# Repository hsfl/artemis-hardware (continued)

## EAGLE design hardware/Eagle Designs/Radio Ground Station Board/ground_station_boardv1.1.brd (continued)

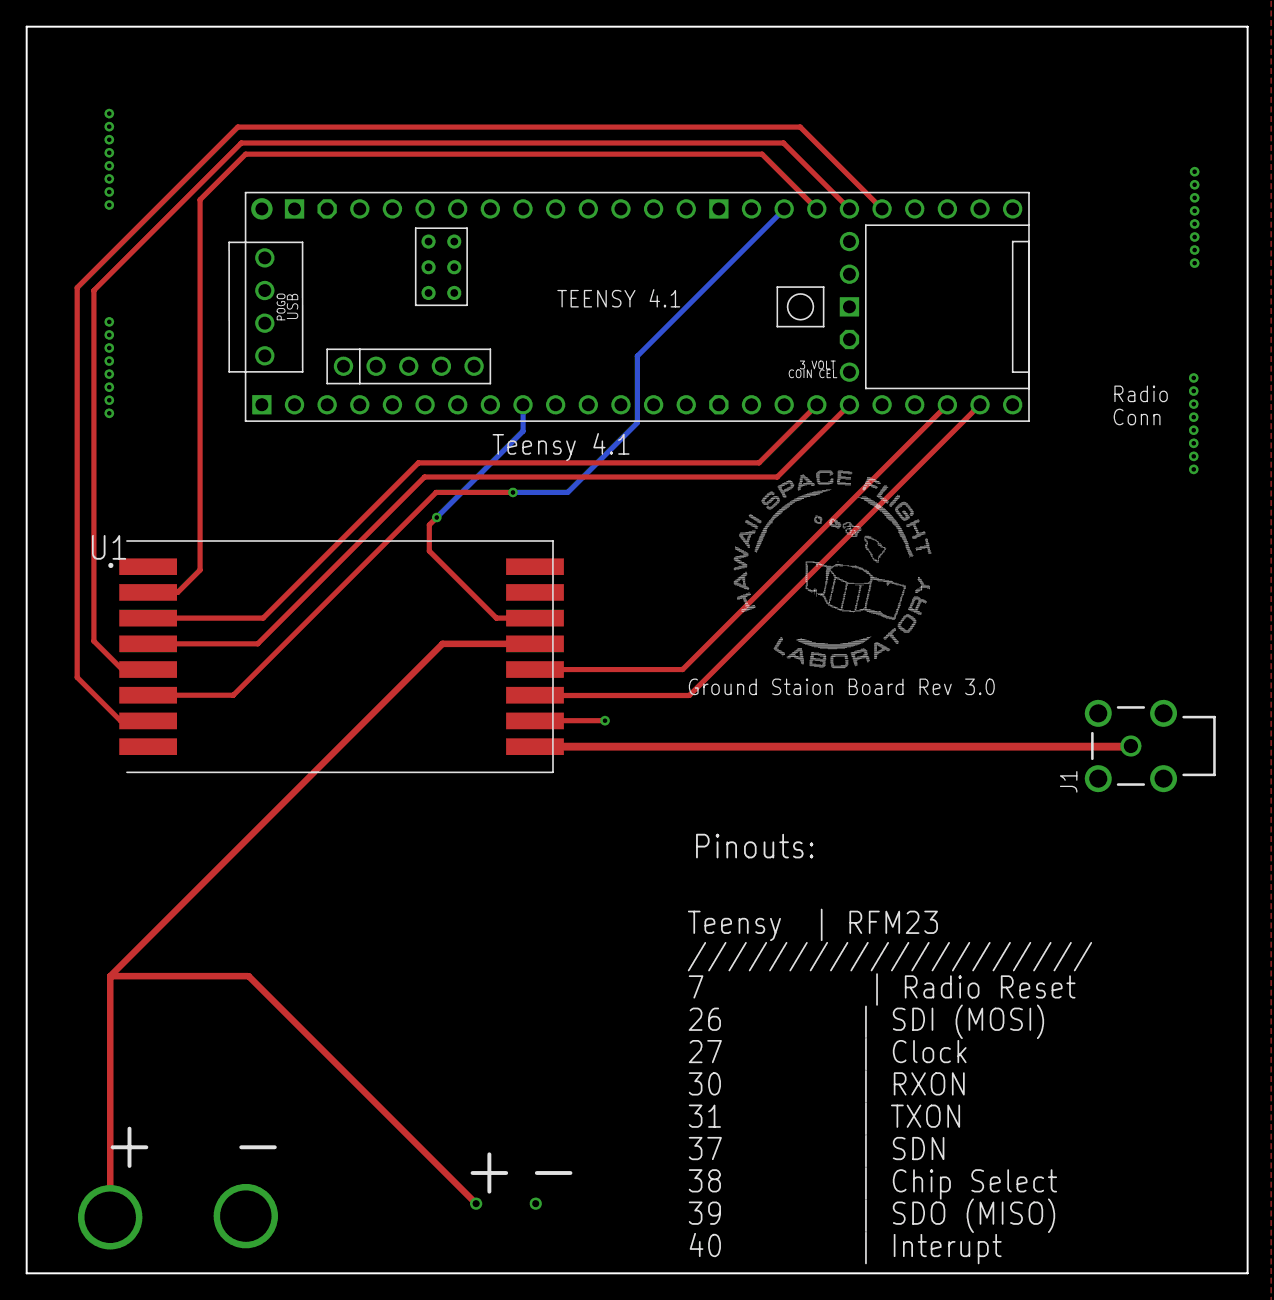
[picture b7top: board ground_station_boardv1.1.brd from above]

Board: 4 copper layers, 95.0 x 97.0 mm, 3 parts (0 on the bottom side), 12 nets.

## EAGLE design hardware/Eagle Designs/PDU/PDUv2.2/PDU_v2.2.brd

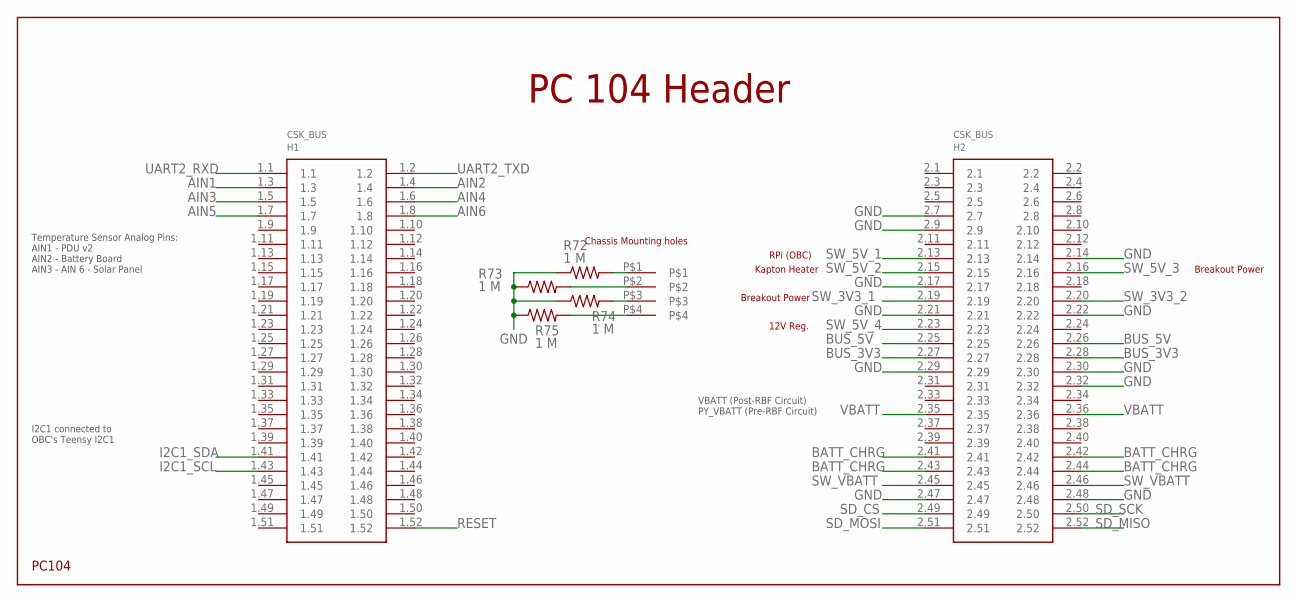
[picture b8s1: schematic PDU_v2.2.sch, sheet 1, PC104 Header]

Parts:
H1: PC104_WCONN
R72, R73, R74, R75: 1 M; 0603-RES

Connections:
AIN1: H1.1.3; also elsewhere on the board
AIN2: H1.1.4; also elsewhere on the board
AIN3: H1.1.5; also elsewhere on the board
AIN4: H1.1.6; also elsewhere on the board
AIN5: H1.1.7; also elsewhere on the board
AIN6: H1.1.8; also elsewhere on the board
BATT_CHRG: H1.2.41, H1.2.42, H1.2.43, H1.2.44; also elsewhere on the board
BUS_3V3: H1.2.27, H1.2.28; also elsewhere on the board
BUS_5V: H1.2.25, H1.2.26; also elsewhere on the board
GND: H1.2.7, H1.2.9, H1.2.14, H1.2.17, H1.2.21, H1.2.22, H1.2.29, H1.2.30, H1.2.32, H1.2.47, H1.2.48, R72.1, R73.1, R74.1, R75.1; also elsewhere on the board
I2C1_SCL: H1.1.43; also elsewhere on the board
I2C1_SDA: H1.1.41; also elsewhere on the board
unnamed: H1.P$1, R72.2
unnamed: H1.P$4, R75.2
unnamed: H1.P$2, R73.2
unnamed: H1.P$3, R74.2
RESET: H1.1.52; also elsewhere on the board
SD_CS: H1.2.49; also elsewhere on the board
SD_MISO: H1.2.52; also elsewhere on the board
SD_MOSI: H1.2.51; also elsewhere on the board
SD_SCK: H1.2.50; also elsewhere on the board
SW_3V3_1: H1.2.19; also elsewhere on the board
SW_3V3_2: H1.2.20; also elsewhere on the board
SW_5V_1: H1.2.13; also elsewhere on the board
SW_5V_2: H1.2.15; also elsewhere on the board
SW_5V_3: H1.2.16; also elsewhere on the board
SW_5V_4: H1.2.23; also elsewhere on the board
SW_VBATT: H1.2.45, H1.2.46; also elsewhere on the board
UART2_RXD: H1.1.1; also elsewhere on the board
UART2_TXD: H1.1.2; also elsewhere on the board
VBATT: H1.2.35, H1.2.36; also elsewhere on the board

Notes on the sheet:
PC 104 Header
Temperature Sensor Analog Pins: AIN1 - PDU v2 AIN2 - Battery Board AIN3 - AIN 6 - Solar Panel
VBATT (Post-RBF Circuit) PY_VBATT (Pre-RBF Circuit)
Kapton Heater
RPi (OBC)
12V Reg.
Breakout Power
I2C1 connected to OBC's Teensy I2C1

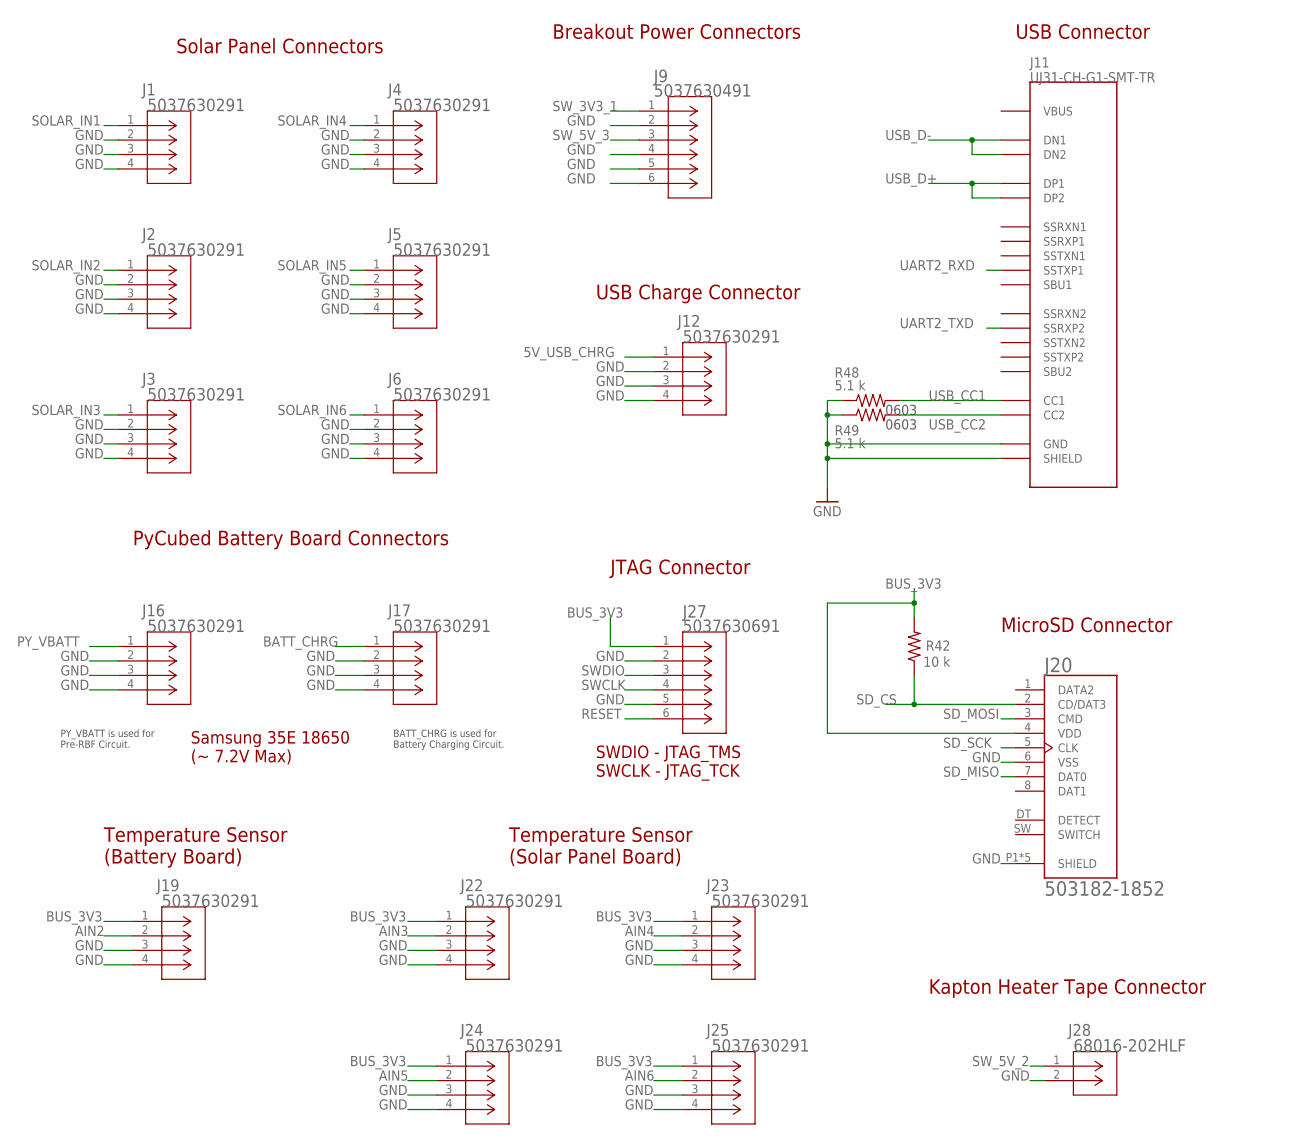
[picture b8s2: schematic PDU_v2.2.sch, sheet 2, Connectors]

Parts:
J1, J2, J3, J4, J5, J6, J12, J16, J17, J19, J22, J23, J24, J25: 5037630291; CON_5037630291
J9: 5037630491; CON_5037630491
J11: UJ31-CH-G1-SMT-TR; CUI_UJ31-CH-G1-SMT-TR
J20: 503182-1852; MOLEX_503182-1852
J27: 5037630691; CONN_503763-0691_MOL
J28: 68016-202HLF
R42: 10 k; 0603-RES
R48, R49: 5.1 k; 0603-RES

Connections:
5V_USB_CHRG: J12.1; also elsewhere on the board
AIN2: J19.2; also elsewhere on the board
AIN3: J22.2; also elsewhere on the board
AIN4: J23.2; also elsewhere on the board
AIN5: J24.2; also elsewhere on the board
AIN6: J25.2; also elsewhere on the board
BATT_CHRG: J17.1; also elsewhere on the board
BUS_3V3: J19.1, J20.4 (VDD), J22.1, J23.1, J24.1, J25.1, J27.1, R42.2; also elsewhere on the board
GND: J1.2, J1.3, J1.4, J2.2, J2.3, J2.4, J3.2, J3.3, J3.4, J4.2, J4.3, J4.4, J5.2, J5.3, J5.4, J6.2, J6.3, J6.4, J9.2, J9.4, J9.5, J9.6, J11.A1 (GND), J11.A12 (GND), J11.B1 (GND), J11.B12 (GND), J11.SH1 (SHIELD), J11.SH2 (SHIELD), J11.SH3 (SHIELD), J11.SH4 (SHIELD), J11.SH5 (SHIELD), J11.SH6 (SHIELD), J12.2, J12.3, J12.4, J16.2, J16.3, J16.4, J17.2, J17.3, J17.4, J19.3, J19.4, J20.6 (VSS), J20.P1 (SHIELD), J20.P2 (SHIELD), J20.P3 (SHIELD), J20.P4 (SHIELD), J20.P5 (SHIELD), J22.3, J22.4, J23.3, J23.4, J24.3, J24.4, J25.3, J25.4, J27.2, J27.5, J28.2, R48.1, R49.1; also elsewhere on the board
PY_VBATT: J16.1; also elsewhere on the board
RESET: J27.6; also elsewhere on the board
SD_CS: J20.2 (CD/DAT3), R42.1; also elsewhere on the board
SD_MISO: J20.7 (DAT0); also elsewhere on the board
SD_MOSI: J20.3 (CMD); also elsewhere on the board
SD_SCK: J20.5 (CLK); also elsewhere on the board
SOLAR_IN1: J1.1; also elsewhere on the board
SOLAR_IN2: J2.1; also elsewhere on the board
SOLAR_IN3: J3.1; also elsewhere on the board
SOLAR_IN4: J4.1; also elsewhere on the board
SOLAR_IN5: J5.1; also elsewhere on the board
SOLAR_IN6: J6.1; also elsewhere on the board
SWCLK: J27.4; also elsewhere on the board
SWDIO: J27.3; also elsewhere on the board
SW_3V3_1: J9.1; also elsewhere on the board
SW_5V_2: J28.1; also elsewhere on the board
SW_5V_3: J9.3; also elsewhere on the board
UART2_RXD: J11.A2 (SSTXP1); also elsewhere on the board
UART2_TXD: J11.A11 (SSRXP2); also elsewhere on the board
USB_CC1: J11.A5 (CC1), R48.2
USB_CC2: J11.B5 (CC2), R49.2
USB_D+: J11.A6 (DP1), J11.B6 (DP2); also elsewhere on the board
USB_D-: J11.A7 (DN1), J11.B7 (DN2); also elsewhere on the board
VBUS: J11.A4 (VBUS), J11.A9 (VBUS), J11.B4 (VBUS), J11.B9 (VBUS)

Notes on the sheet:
USB Charge Connector
Solar Panel Connectors
Breakout Power Connectors
USB Connector
MicroSD Connector
JTAG Connector
SWDIO - JTAG_TMS SWCLK - JTAG_TCK
PyCubed Battery Board Connectors
Samsung 35E 18650 (~ 7.2V Max)
Kapton Heater Tape Connector
Temperature Sensor (Solar Panel Board)
Temperature Sensor (Battery Board)
0603
PY_VBATT is used for Pre-RBF Circuit.
BATT_CHRG is used for Battery Charging Circuit.

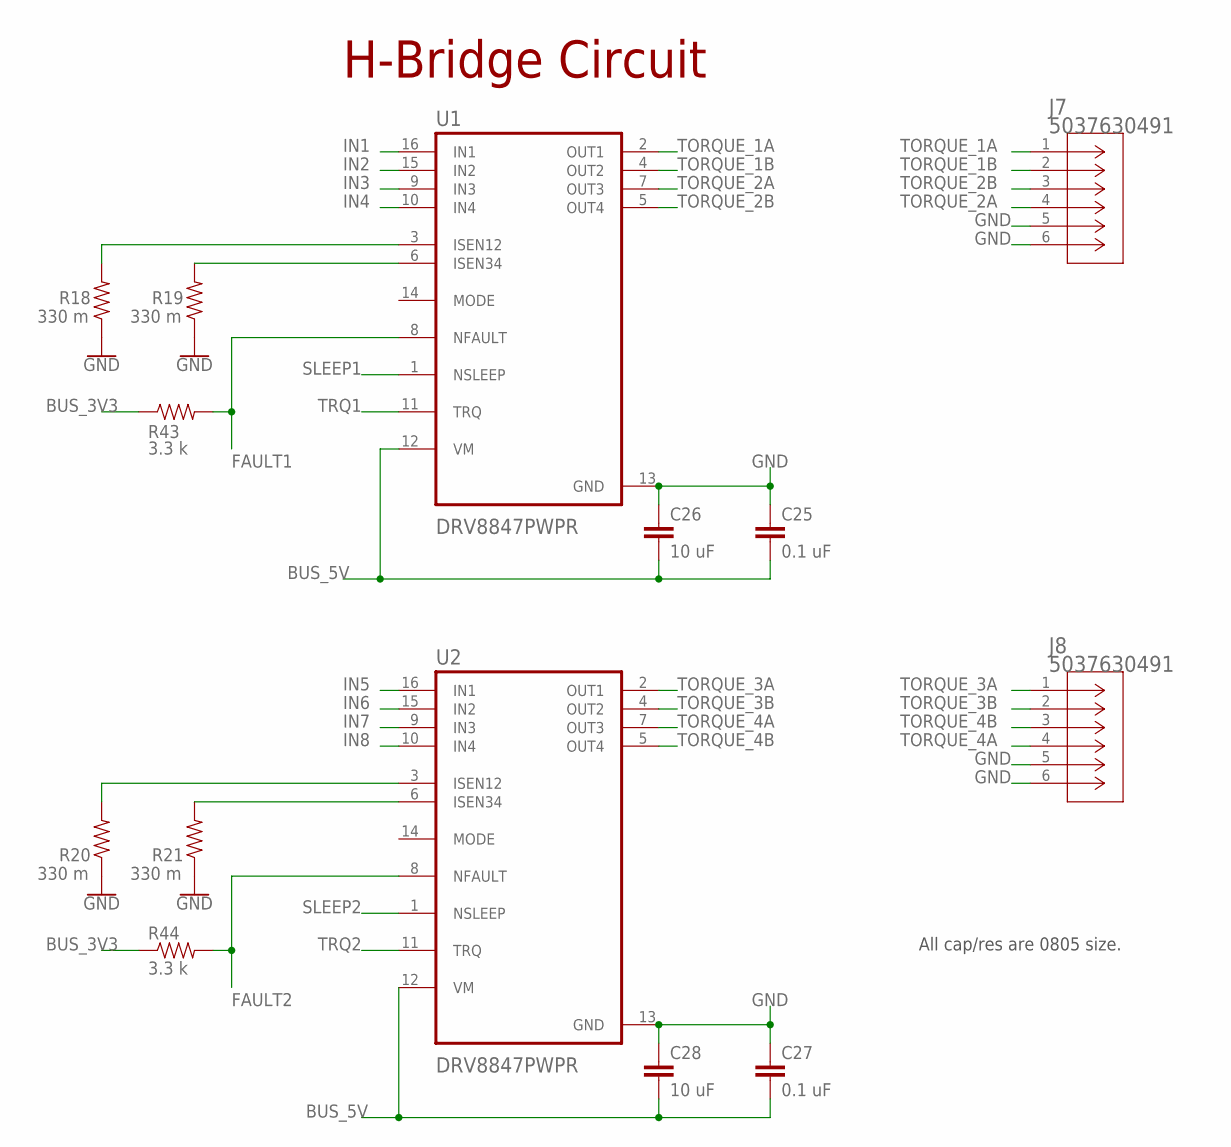
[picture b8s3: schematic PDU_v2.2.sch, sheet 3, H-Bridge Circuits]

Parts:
C25, C27: 0.1 uF; 0805
C26, C28: 10 uF; 0805
J7, J8: 5037630491; CON_5037630491
R18, R19, R20, R21: 330 m; 0805
R43, R44: 3.3 k; 0805
U1, U2: DRV8847PWPR; SOP65P640X120-17N

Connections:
BUS_3V3: R43.1, R44.1; also elsewhere on the board
BUS_5V: C25.2, C26.2, C27.2, C28.2, U1.12 (VM), U2.12 (VM); also elsewhere on the board
FAULT1: R43.2, U1.8 (NFAULT); also elsewhere on the board
FAULT2: R44.2, U2.8 (NFAULT); also elsewhere on the board
GND: C25.1, C26.1, C27.1, C28.1, J7.5, J7.6, J8.5, J8.6, R18.1, R19.1, R20.1, R21.1, U1.13 (GND), U2.13 (GND); also elsewhere on the board
IN1: U1.16 (IN1); also elsewhere on the board
IN2: U1.15 (IN2); also elsewhere on the board
IN3: U1.9 (IN3); also elsewhere on the board
IN4: U1.10 (IN4); also elsewhere on the board
IN5: U2.16 (IN1); also elsewhere on the board
IN6: U2.15 (IN2); also elsewhere on the board
IN7: U2.9 (IN3); also elsewhere on the board
IN8: U2.10 (IN4); also elsewhere on the board
unnamed: R19.2, U1.6 (ISEN34)
unnamed: R18.2, U1.3 (ISEN12)
unnamed: R21.2, U2.6 (ISEN34)
unnamed: R20.2, U2.3 (ISEN12)
SLEEP1: U1.1 (NSLEEP); also elsewhere on the board
SLEEP2: U2.1 (NSLEEP); also elsewhere on the board
TORQUE_1A: J7.1, U1.2 (OUT1)
TORQUE_1B: J7.2, U1.4 (OUT2)
TORQUE_2A: J7.4, U1.7 (OUT3)
TORQUE_2B: J7.3, U1.5 (OUT4)
TORQUE_3A: J8.1, U2.2 (OUT1)
TORQUE_3B: J8.2, U2.4 (OUT2)
TORQUE_4A: J8.4, U2.7 (OUT3)
TORQUE_4B: J8.3, U2.5 (OUT4)
TRQ1: U1.11 (TRQ); also elsewhere on the board
TRQ2: U2.11 (TRQ); also elsewhere on the board

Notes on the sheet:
H-Bridge Circuit
All cap/res are 0805 size.

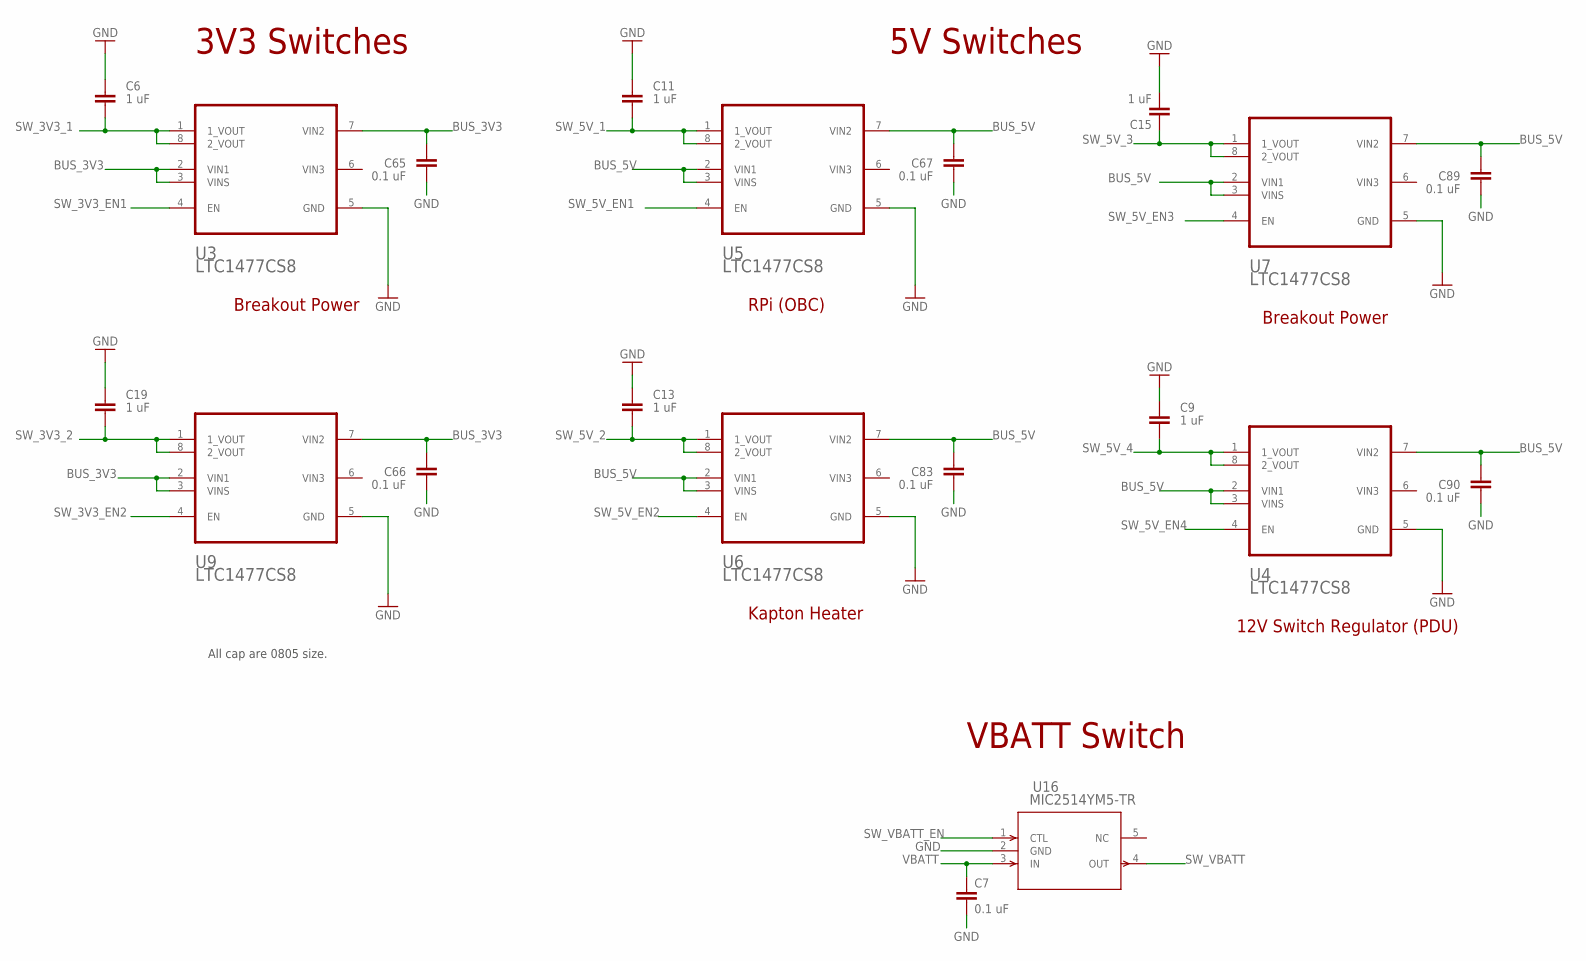
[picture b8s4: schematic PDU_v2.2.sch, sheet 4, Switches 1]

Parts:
C6, C9, C11, C13, C15, C19: 1 uF; 0805
C7, C65, C66, C67, C83, C89, C90: 0.1 uF; 0805
U3, U4, U5, U6, U7, U9: LTC1477CS8LINEAR_TECHNOLOGY_LTC1477CS8_0_2; LINEAR_TECHNOLOGY_LTC1477CS8_2
U16: MIC2514YM5-TR; SOT-23-5_M5_MCH

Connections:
BUS_3V3: C65.1, C66.1, U3.2 (VIN1), U3.3 (VINS), U3.7 (VIN2), U9.2 (VIN1), U9.3 (VINS), U9.7 (VIN2); also elsewhere on the board
BUS_5V: C67.1, C83.1, C89.1, C90.1, U4.2 (VIN1), U4.3 (VINS), U4.7 (VIN2), U5.2 (VIN1), U5.3 (VINS), U5.7 (VIN2), U6.2 (VIN1), U6.3 (VINS), U6.7 (VIN2), U7.2 (VIN1), U7.3 (VINS), U7.7 (VIN2); also elsewhere on the board
GND: C6.2, C7.2, C9.2, C11.2, C13.2, C15.2, C19.2, C65.2, C66.2, C67.2, C83.2, C89.2, C90.2, U3.5 (GND), U4.5 (GND), U5.5 (GND), U6.5 (GND), U7.5 (GND), U9.5 (GND), U16.2 (GND); also elsewhere on the board
SW_3V3_1: C6.1, U3.1 (1_VOUT), U3.8 (2_VOUT); also elsewhere on the board
SW_3V3_2: C19.1, U9.1 (1_VOUT), U9.8 (2_VOUT); also elsewhere on the board
SW_3V3_EN1: U3.4 (EN); also elsewhere on the board
SW_3V3_EN2: U9.4 (EN); also elsewhere on the board
SW_5V_1: C11.1, U5.1 (1_VOUT), U5.8 (2_VOUT); also elsewhere on the board
SW_5V_2: C13.1, U6.1 (1_VOUT), U6.8 (2_VOUT); also elsewhere on the board
SW_5V_3: C15.1, U7.1 (1_VOUT), U7.8 (2_VOUT); also elsewhere on the board
SW_5V_4: C9.1, U4.1 (1_VOUT), U4.8 (2_VOUT); also elsewhere on the board
SW_5V_EN1: U5.4 (EN); also elsewhere on the board
SW_5V_EN2: U6.4 (EN); also elsewhere on the board
SW_5V_EN3: U7.4 (EN); also elsewhere on the board
SW_5V_EN4: U4.4 (EN); also elsewhere on the board
SW_VBATT: U16.4 (OUT); also elsewhere on the board
SW_VBATT_EN: U16.1 (CTL); also elsewhere on the board
VBATT: C7.1, U16.3 (IN); also elsewhere on the board
VIN3: U3.6 (VIN3), U4.6 (VIN3), U5.6 (VIN3), U6.6 (VIN3), U7.6 (VIN3), U9.6 (VIN3)

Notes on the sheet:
3V3 Switches
5V Switches
Breakout Power
RPi (OBC)
Kapton Heater
All cap are 0805 size.
12V Switch Regulator (PDU)
VBATT Switch

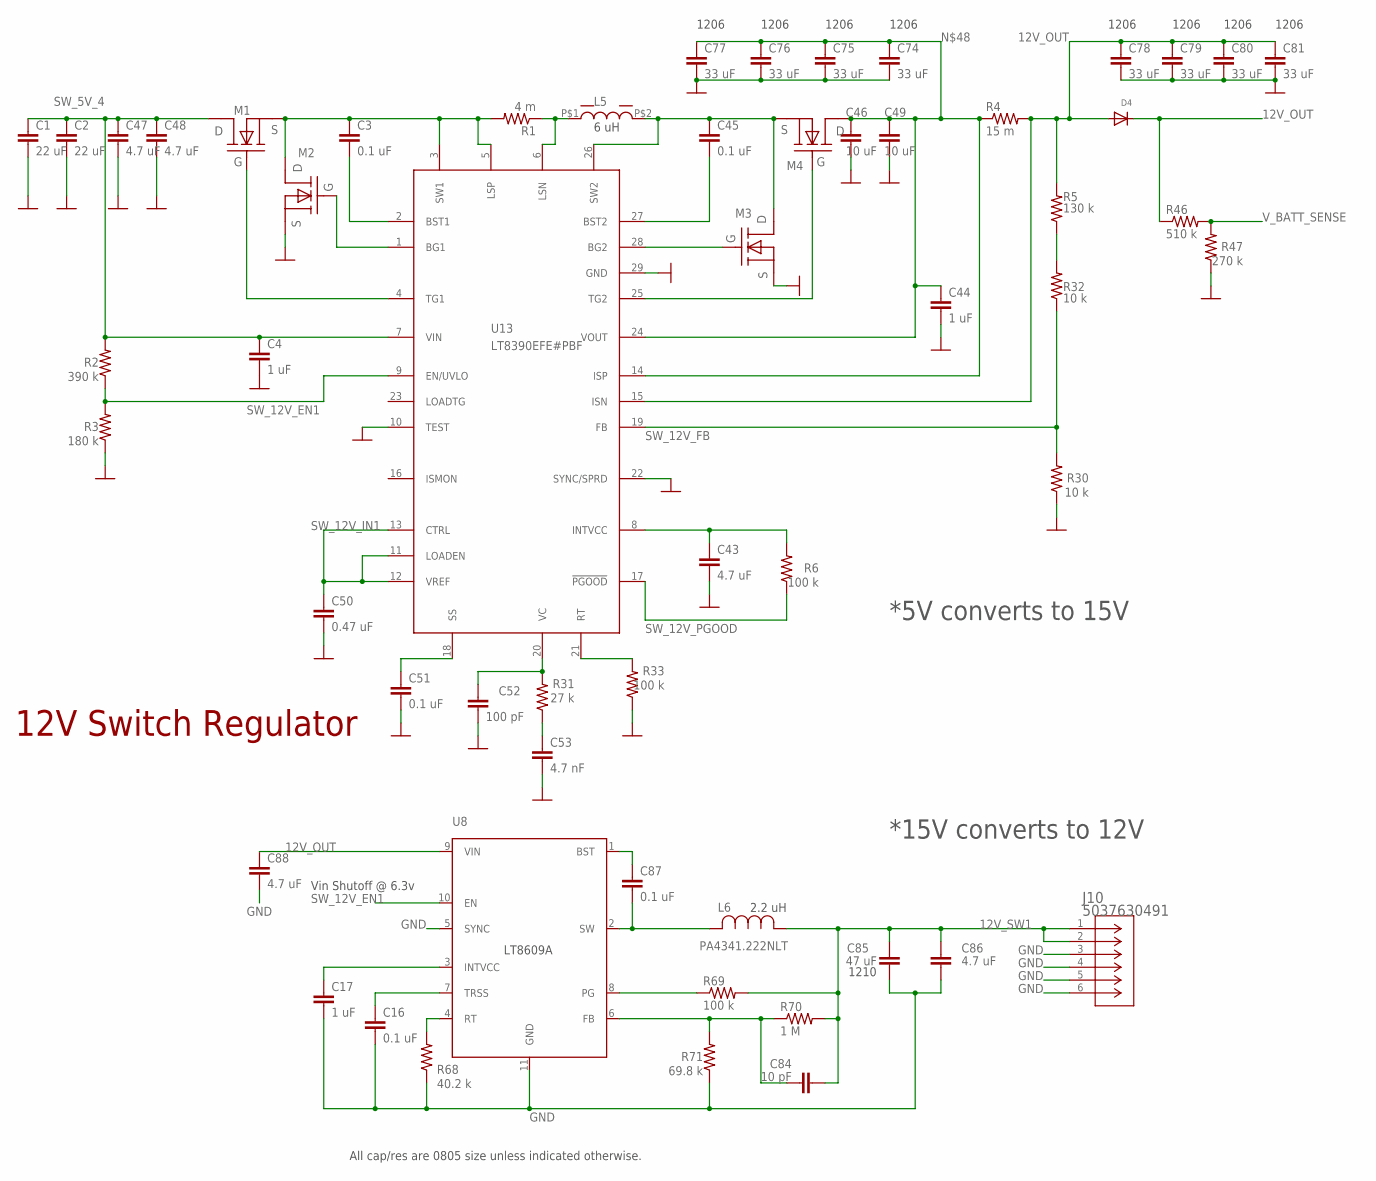
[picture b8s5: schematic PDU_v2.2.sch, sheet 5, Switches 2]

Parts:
C1, C2: 22 uF; 0805
C3, C16, C45, C51, C87: 0.1 uF; 0805
C4, C17, C44: 1 uF; 0805
C43, C47, C48, C86, C88: 4.7 uF; 0805
C46, C49: 10 uF; 0805
C50: 0.47 uF; 0805
C52: 100 pF; 0805
C53: 4.7 nF; 0805
C74, C75, C76, C77, C78, C79, C80, C81: 33 uF; 1206
C84: 10 pF; 0805
C85: 47 uF; 1210
D4: DIODE_SOD-123FL; SOD-123FL
J10: 5037630491; CON_5037630491
L5: 6 uH; 7443551600
L6: PA4341.222NLT; IND_222NLT_PUL
M1, M2: BSZ100N06LS3
M3, M4: BSZ033NE2LS5; BSZ100N06LS3
R1: 4 m; 0805
R2: 390 k; 0805
R3: 180 k; 0805
R4: 15 m; 0805
R5: 130 k; 0805
R6, R33, R69: 100 k; 0805
R30, R32: 10 k; 0805
R31: 27 k; 0805
R46: 510 k; 0805
R47: 270 k; 0805
R68: 40.2 k; 0805
R70: 1 M; 0805
R71: 69.8 k; 0805
U8: LT8609A; MSOP-10_MSE
U13: LT8390EFE#PBF; SOP65P640X120-29N

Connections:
12V_OUT: C78.1, C79.1, C80.1, C81.1, C88.1, D4.A, D4.C, R4.2, R5.2, R46.1, U8.9 (VIN), U13.15 (ISN)
12V_SW1: C84.2, C85.1, C86.1, J10.1, J10.2, L6.1, R69.2, R70.2
BST_3V3_BUS: C87.1, U8.1 (BST)
FB_3V3_BUS: C84.1, R70.1, R71.2, U8.6 (FB)
GND: C1.2, C2.2, C4.2, C16.2, C17.2, C43.2, C44.2, C46.2, C47.2, C48.2, C49.2, C50.2, C51.2, C52.2, C53.2, C74.2, C75.2, C76.2, C77.2, C78.2, C79.2, C80.2, C81.2, C85.2, C86.2, C88.2, J10.3, J10.4, J10.5, J10.6, M2.P$2 (S), M2.P$3 (S), M2.P$4 (S), M3.P$2 (S), M3.P$3 (S), M3.P$4 (S), R3.1, R30.1, R33.1, R47.1, R68.1, R71.1, U8.5 (SYNC), U8.11 (GND), U13.10 (TEST), U13.22 (SYNC/SPRD), U13.29 (GND); also elsewhere on the board
unnamed: C3.1, M1.P$2 (S), M1.P$3 (S), M1.P$4 (S), M2.P$5 (D), M2.P$6 (D), M2.P$7 (D), M2.P$8 (D), M2.P$9 (D), R1.2, U13.3 (SW1), U13.5 (LSP)
unnamed: C3.2, U13.2 (BST1)
unnamed: M2.P$1 (G), U13.1 (BG1)
unnamed: M1.P$1 (G), U13.4 (TG1)
unnamed: M3.P$1 (G), U13.28 (BG2)
unnamed: C52.1, R31.2, U13.20 (VC)
unnamed: R5.1, R32.2
unnamed: C45.1, L5.P$2, M3.P$5 (D), M3.P$6 (D), M3.P$7 (D), M3.P$8 (D), M3.P$9 (D), M4.P$2 (S), M4.P$3 (S), M4.P$4 (S), U13.26 (SW2)
unnamed: C43.1, R6.2, U13.8 (INTVCC)
unnamed: L5.P$1, R1.1, U13.6 (LSN)
unnamed: C45.2, U13.27 (BST2)
unnamed: C44.1, C46.1, C49.1, C74.1, C75.1, C76.1, C77.1, M4.P$5 (D), M4.P$6 (D), M4.P$7 (D), M4.P$8 (D), M4.P$9 (D), R4.1, U13.14 (ISP), U13.24 (VOUT)
unnamed: M4.P$1 (G), U13.25 (TG2)
unnamed: C51.1, U13.18 (SS)
unnamed: R33.2, U13.21 (RT)
unnamed: C53.1, R31.1
PG_3V3_BUS: R69.1, U8.8 (PG)
RT_3V3_BUS: R68.2, U8.4 (RT)
SW_3V3_BUS: C87.2, L6.2, U8.2 (SW)
SW_5V_4: C1.1, C2.1, C4.1, C47.1, C48.1, M1.P$5 (D), M1.P$6 (D), M1.P$7 (D), M1.P$8 (D), M1.P$9 (D), R2.2, U13.7 (VIN); also elsewhere on the board
SW_12V_EN1: R2.1, R3.2, U8.10 (EN), U13.9 (EN/UVLO)
SW_12V_FB: R30.2, R32.1, U13.19 (FB)
SW_12V_IN1: C50.1, U13.11 (LOADEN), U13.12 (VREF), U13.13 (CTRL)
SW_12V_PGOOD: R6.1, U13.17 (!PGOOD)
TRSS_3V3_BUS: C16.1, U8.7 (TRSS)
VCC_3V3_BUS: C17.1, U8.3 (INTVCC)
V_BATT_SENSE: R46.2, R47.2

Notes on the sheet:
Vin Shutoff @ 6.3v
12V Switch Regulator
6 uH
1206
2.2 uH
1210
All cap/res are 0805 size unless indicated otherwise.
*15V converts to 12V
*5V converts to 15V

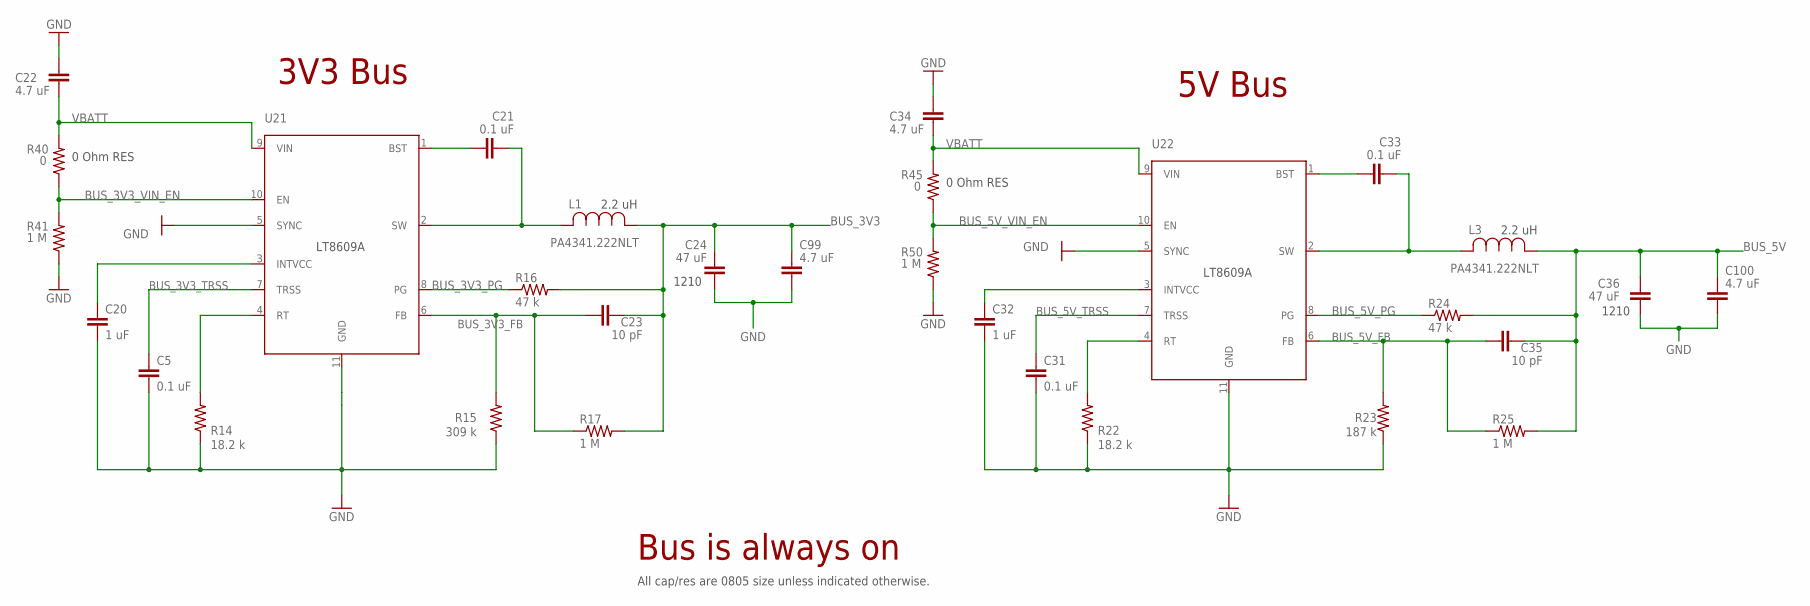
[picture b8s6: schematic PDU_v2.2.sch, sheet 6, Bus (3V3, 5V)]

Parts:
C5, C21, C31, C33: 0.1 uF; 0805
C20, C32: 1 uF; 0805
C22, C34, C99, C100: 4.7 uF; 0805
C23, C35: 10 pF; 0805
C24, C36: 47 uF; 1210
L1, L3: PA4341.222NLT; IND_222NLT_PUL
R14, R22: 18.2 k; 0805
R15: 309 k; 0805
R16, R24: 47 k; 0805
R17, R25, R41, R50: 1 M; 0805
R23: 187 k; 0805
R40, R45: 0; 0805
U21, U22: LT8609A; MSOP-10_MSE

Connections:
BUS_3V3: C23.2, C24.1, C99.1, L1.1, R16.2, R17.2; also elsewhere on the board
BUS_3V3_FB: C23.1, R15.2, R17.1, U21.6 (FB)
BUS_3V3_PG: R16.1, U21.8 (PG)
BUS_3V3_TRSS: C5.1, U21.7 (TRSS)
BUS_3V3_VIN_EN: R40.1, R41.2, U21.10 (EN)
BUS_5V: C35.2, C36.1, C100.1, L3.1, R24.2, R25.2; also elsewhere on the board
BUS_5V_FB: C35.1, R23.2, R25.1, U22.6 (FB)
BUS_5V_PG: R24.1, U22.8 (PG)
BUS_5V_TRSS: C31.1, U22.7 (TRSS)
BUS_5V_VIN_EN: R45.1, R50.2, U22.10 (EN)
GND: C5.2, C20.2, C22.2, C24.2, C31.2, C32.2, C34.2, C36.2, C99.2, C100.2, R14.1, R15.1, R22.1, R23.1, R41.1, R50.1, U21.5 (SYNC), U21.11 (GND), U22.5 (SYNC), U22.11 (GND); also elsewhere on the board
unnamed: C20.1, U21.3 (INTVCC)
unnamed: R14.2, U21.4 (RT)
unnamed: C21.1, U21.1 (BST)
unnamed: C21.2, L1.2, U21.2 (SW)
unnamed: R22.2, U22.4 (RT)
unnamed: C32.1, U22.3 (INTVCC)
unnamed: C33.1, U22.1 (BST)
unnamed: C33.2, L3.2, U22.2 (SW)
VBATT: C22.1, C34.1, R40.2, R45.2, U21.9 (VIN), U22.9 (VIN); also elsewhere on the board

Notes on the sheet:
0 Ohm RES
Bus is always on
3V3 Bus
5V Bus
2.2 uH
1210
All cap/res are 0805 size unless indicated otherwise.

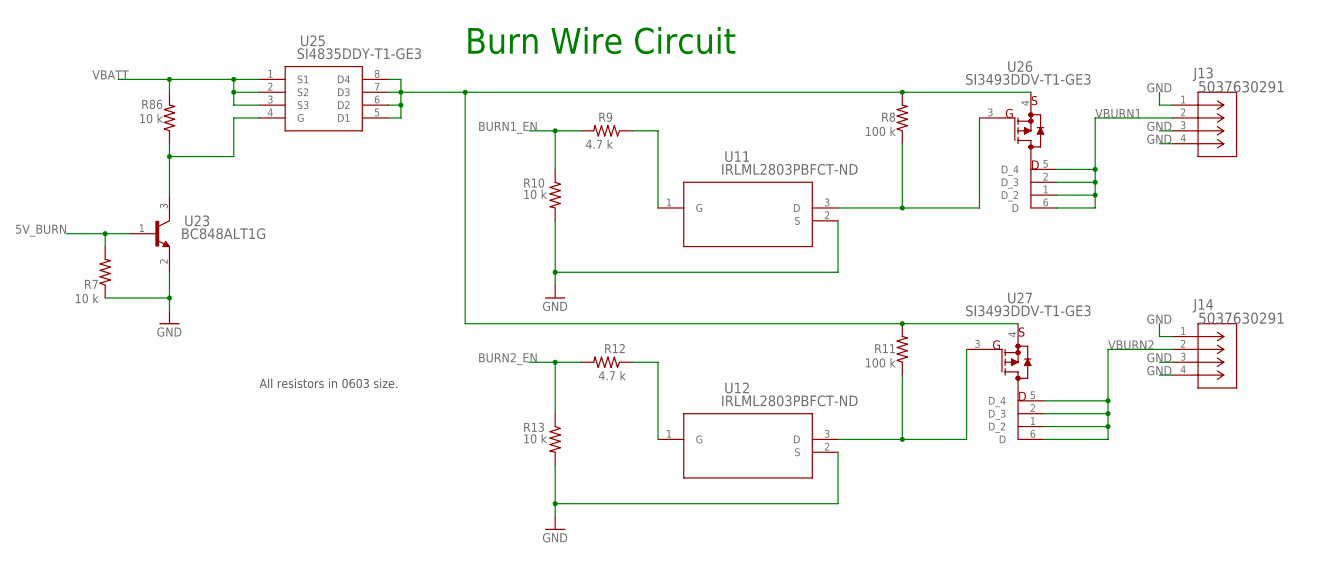
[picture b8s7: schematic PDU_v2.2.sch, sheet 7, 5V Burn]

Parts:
J13, J14: 5037630291; CON_5037630291
R7, R10, R13, R86: 10 k; 0603-RES
R8, R11: 100 k; 0603-RES
R9, R12: 4.7 k; 0603-RES
U11, U12: IRLML2803PBFCT-ND; PG-TO23-3_INF
U23: BC848ALT1G; SOT-23_ONS
U25: SI4835DDY-T1-GE3; SOIC_DY-T1-GE3_VIS
U26, U27: SI3493DDV-T1-GE3; 6TSOP_VIS

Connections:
5V_BURN: R7.2, U23.1 (BASE); also elsewhere on the board
BURN1_EN: R9.2, R10.1; also elsewhere on the board
BURN2_EN: R12.2, R13.1; also elsewhere on the board
GND: J13.1, J13.3, J13.4, J14.1, J14.3, J14.4, R7.1, R10.2, R13.2, U11.2 (S), U12.2 (S), U23.2 (EMITTER); also elsewhere on the board
unnamed: R8.2, R11.2, U25.5 (D1), U25.6 (D2), U25.7 (D3), U25.8 (D4), U26.4 (S), U27.4 (S)
unnamed: R12.1, U12.1 (G)
unnamed: R11.1, U12.3 (D), U27.3 (G)
unnamed: R86.1, U23.3 (COLLECTOR), U25.4 (G)
unnamed: R9.1, U11.1 (G)
unnamed: R8.1, U11.3 (D), U26.3 (G)
VBATT: R86.2, U25.1 (S1), U25.2 (S2), U25.3 (S3); also elsewhere on the board
VBURN1: J13.2, U26.1 (D_2), U26.2 (D_3), U26.5 (D_4), U26.6 (D)
VBURN2: J14.2, U27.1 (D_2), U27.2 (D_3), U27.5 (D_4), U27.6 (D)

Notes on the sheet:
Burn Wire Circuit
All resistors in 0603 size.

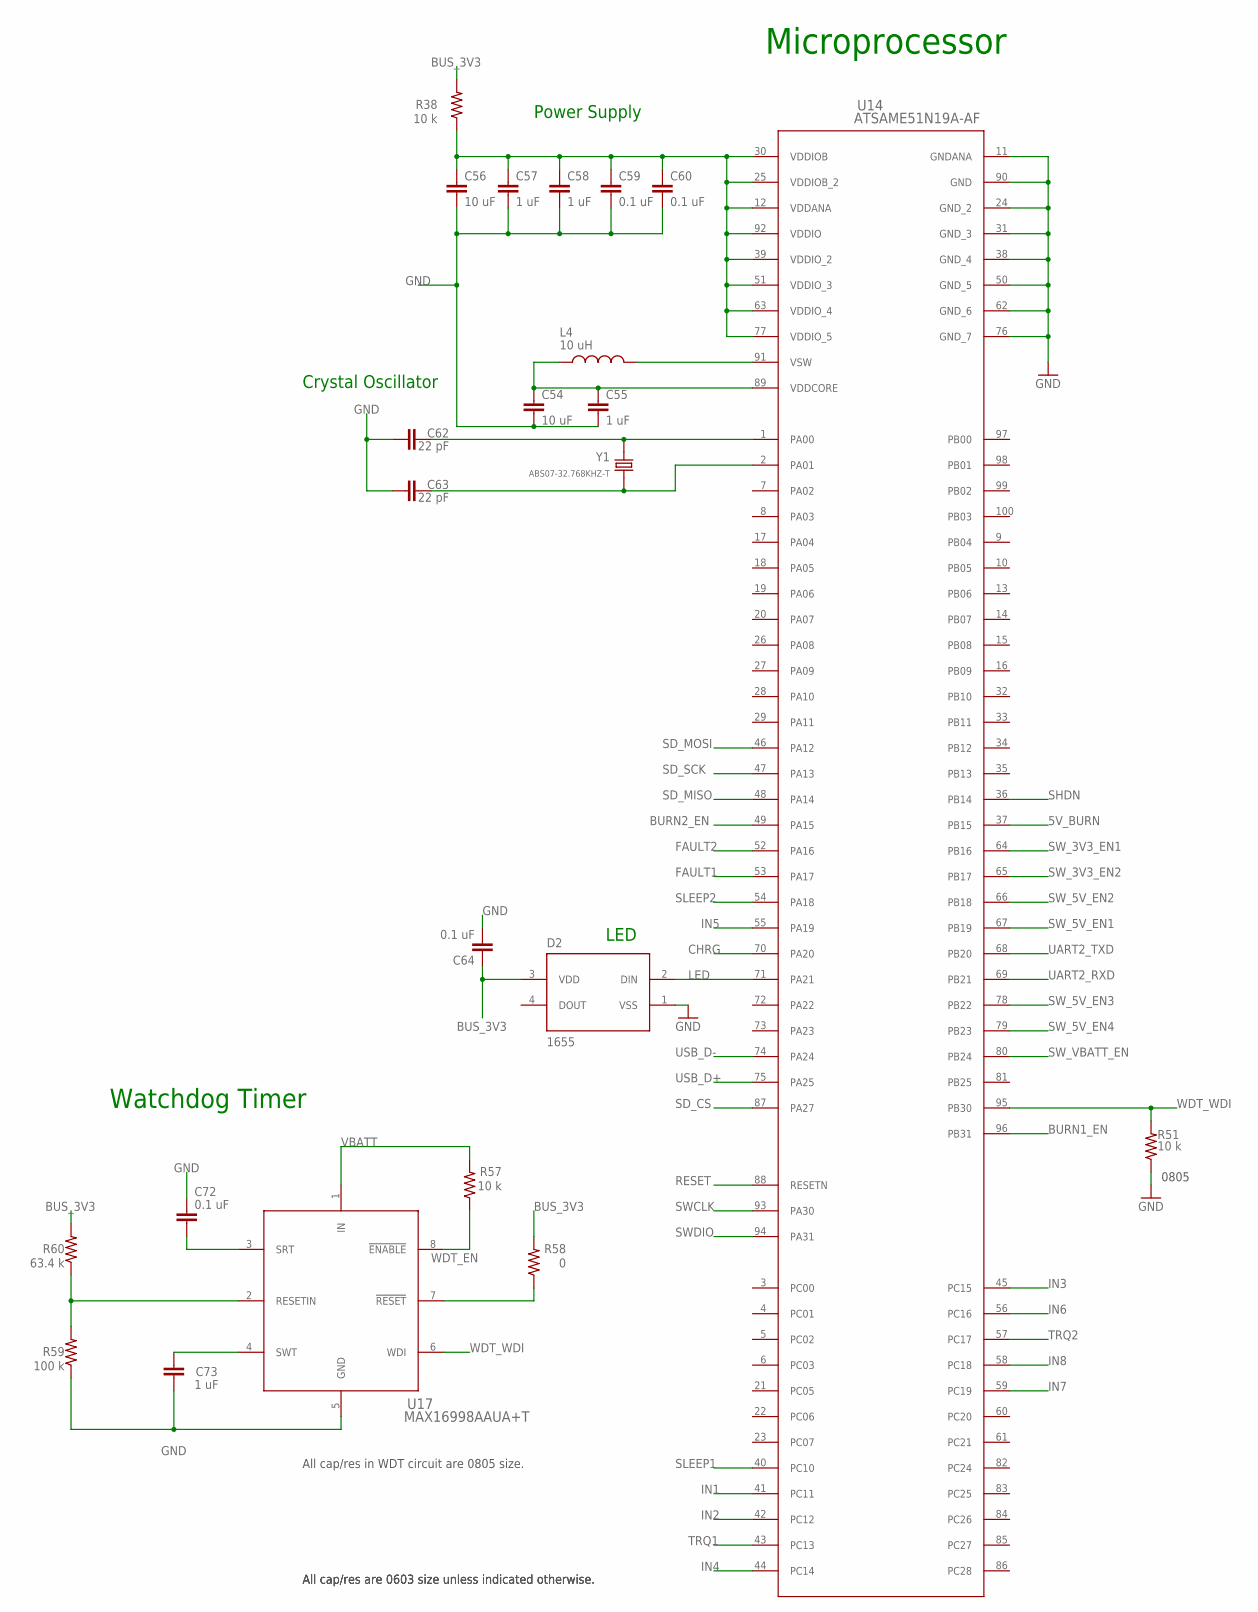
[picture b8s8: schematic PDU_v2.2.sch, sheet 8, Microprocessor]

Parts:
C54, C56: 10 uF; 0603-CAP
C55, C57, C58: 1 uF; 0603-CAP
C59, C60, C64: 0.1 uF; 0603-CAP
C62, C63: 22 pF; 0603-CAP
C72: 0.1 uF; 0805
C73: 1 uF; 0805
D2: 1655; LED_1655
L4: 10 uH; INDC2012X100N
R38: 10 k; 0603-RES
R51, R57: 10 k; 0805
R58: 0; 0805
R59: 100 k; 0805
R60: 63.4 k; 0805
U14: ATSAME51N19A-AF; TQFP100_14X14MC_MCH
U17: MAX16998AAUA+T; 21-0036K_MXM
Y1: ABS07-32.768KHZ-T; XTAL_ABS07-32.768KHZ-T

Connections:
5V_BURN: U14.37 (PB15); also elsewhere on the board
BURN1_EN: U14.96 (PB31); also elsewhere on the board
BURN2_EN: U14.49 (PA15); also elsewhere on the board
BUS_3V3: C64.1, D2.3 (VDD), R38.2, R58.2, R60.2; also elsewhere on the board
CCO_0: C62.2, U14.1 (PA00), Y1.2
CCO_1: C63.2, U14.2 (PA01), Y1.1
CHRG: U14.70 (PA20); also elsewhere on the board
FAULT1: U14.53 (PA17); also elsewhere on the board
FAULT2: U14.52 (PA16); also elsewhere on the board
GND: C54.2, C55.2, C56.2, C57.2, C58.2, C59.2, C60.2, C62.1, C63.1, C64.2, C72.1, C73.2, D2.1 (VSS), R51.1, R59.1, U14.11 (GNDANA), U14.24 (GND_2), U14.31 (GND_3), U14.38 (GND_4), U14.50 (GND_5), U14.62 (GND_6), U14.76 (GND_7), U14.90 (GND), U17.5 (GND); also elsewhere on the board
IN1: U14.41 (PC11); also elsewhere on the board
IN2: U14.42 (PC12); also elsewhere on the board
IN3: U14.45 (PC15); also elsewhere on the board
IN4: U14.44 (PC14); also elsewhere on the board
IN5: U14.55 (PA19); also elsewhere on the board
IN6: U14.56 (PC16); also elsewhere on the board
IN7: U14.59 (PC19); also elsewhere on the board
IN8: U14.58 (PC18); also elsewhere on the board
LED: D2.2 (DIN), U14.71 (PA21)
unnamed: L4.2, U14.91 (VSW)
unnamed: C54.1, C55.1, L4.1, U14.89 (VDDCORE)
unnamed: C72.2, U17.3 (SRT)
unnamed: C73.1, U17.4 (SWT)
unnamed: R59.2, R60.1, U17.2 (RESETIN)
RESET: R58.1, U14.88 (RESETN), U17.7 (!RESET); also elsewhere on the board
SD_CS: U14.87 (PA27); also elsewhere on the board
SD_MISO: U14.48 (PA14); also elsewhere on the board
SD_MOSI: U14.46 (PA12); also elsewhere on the board
SD_SCK: U14.47 (PA13); also elsewhere on the board
SHDN: U14.36 (PB14); also elsewhere on the board
SLEEP1: U14.40 (PC10); also elsewhere on the board
SLEEP2: U14.54 (PA18); also elsewhere on the board
SWCLK: U14.93 (PA30); also elsewhere on the board
SWDIO: U14.94 (PA31); also elsewhere on the board
SW_3V3_EN1: U14.64 (PB16); also elsewhere on the board
SW_3V3_EN2: U14.65 (PB17); also elsewhere on the board
SW_5V_EN1: U14.67 (PB19); also elsewhere on the board
SW_5V_EN2: U14.66 (PB18); also elsewhere on the board
SW_5V_EN3: U14.78 (PB22); also elsewhere on the board
SW_5V_EN4: U14.79 (PB23); also elsewhere on the board
SW_VBATT_EN: U14.80 (PB24); also elsewhere on the board
TRQ1: U14.43 (PC13); also elsewhere on the board
TRQ2: U14.57 (PC17); also elsewhere on the board
UART2_RXD: U14.69 (PB21); also elsewhere on the board
UART2_TXD: U14.68 (PB20); also elsewhere on the board
USB_D+: U14.75 (PA25); also elsewhere on the board
USB_D-: U14.74 (PA24); also elsewhere on the board
VBATT: R57.2, U17.1 (IN); also elsewhere on the board
VDD: C56.1, C57.1, C58.1, C59.1, C60.1, R38.1, U14.12 (VDDANA), U14.25 (VDDIOB_2), U14.30 (VDDIOB), U14.39 (VDDIO_2), U14.51 (VDDIO_3), U14.63 (VDDIO_4), U14.77 (VDDIO_5), U14.92 (VDDIO)
WDT_EN: R57.1, U17.8 (!ENABLE)
WDT_WDI: R51.2, U14.95 (PB30), U17.6 (WDI)

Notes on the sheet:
Microprocessor
LED
Watchdog Timer
Power Supply
Crystal Oscillator
0805
All cap/res are 0603 size unless indicated otherwise.
All cap/res in WDT circuit are 0805 size.
